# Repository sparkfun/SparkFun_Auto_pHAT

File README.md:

SparkFun Auto pHAT for Raspberry Pi (Qwiic)
========================================

[*SparkFun Auto pHAT for Raspberry Pi (Qwiic) (ROB-16328)*](https://www.sparkfun.com/products/16328)

The SparkFun Auto pHAT for Raspberry Pi is an all in one robotics package that focuses on quickly adding robot functionality and support to your Raspberry Pi or other single-board computer. The Auto pHAT can drive two small DC motors with or without encoders and up to four servo motors in a straightforward manner via an I<sup>2</sup>C connection. The servo control is based on the [SparkFun servo pHAT](https://www.sparkfun.com/products/15316) and thanks to its I<sup>2</sup>C capabilities, this PWM add-on saves the Raspberry Pi's GPIO pins, allowing you to use them for other purposes. We have also provided a Qwiic connector for easy interfacing with the I<sup>2</sup>C bus using the [Qwiic system](https://www.sparkfun.com/qwiic). Whether you use the Auto pHAT with a Raspberry Pi, NVIDIA, Jetson Nano, Google Coral, or other SBC, it makes for a unique robotics addition for and board with a 2x20 GPIO.

The DC motor control comes from the same 4245 PSOC and 2-channel motor ports system used on the [SparkFun Qwiic Motor Driver](https://www.sparkfun.com/products/15451). This provides 1.2A steady state drive per channel (1.5A peak) and 127 levels of DC drive strength. The SparkFun Auto pHAT also supports up to two motor encoders thanks to the onboard ATTINY84A to provide more precise movement to your creation! 

Additionally, the Auto pHAT has an on-board ICM-20948 9DOF IMU for all your motion sensing needs. This enables your robot to access the 3-Axis Gyroscope with four selectable ranges, 3-Axis Accelerometer, again with four selectable ranges, and 3-axis magnetometer with an FSR of ±4900µT.

Power to the SparkFun Auto pHAT can be supplied through USB-C connector or external power. This will power either the motors only, or power the motors as well as the Raspberry Pi that is connected to the HAT. This USB-C connector can also be used to hook up the Pi via serial port connection to avoid having to use a monitor and keyboard for setting up the Pi. We've even added power protection circuits to the design, to avoid damage to power sources.

For reference on programming the ATTINY84:

FUSE BITS:
(Set fuses to run at 8MHz internal)
(Disable Brown Out Detect)

* LowFuse 0xE2 
* HighFuse 0xDF
* ExtendedFuse 0xFF

Repository Contents
-------------------

* **/Documentation** - Data sheets, additional product information
* **/Hardware** - Eagle design files (.brd, .sch)
* **/Hardware/Production** - Production panel files and gerbers (.brd)
* **/Firmware** - Firmware for the Dual Encoder Reader IC (ATTiny84) and the Motor Driver IC (4245 PSOC)

Documentation
--------------

* **[Hookup Guide](https://learn.sparkfun.com/tutorials/sparkfun-auto-phat-hookup-guide)** - Basic hookup guide for the SparkFun Auto pHAT for Raspberry Pi (Qwiic).

License Information
-------------------

This product is _**open source**_! 

Please review the LICENSE.md file for license information. 

If you have any questions or concerns on licensing, please contact technical support on our [SparkFun forums](https://forum.sparkfun.com/viewforum.php?f=152).

Distributed as-is; no warranty is given.

- Your friends at SparkFun.

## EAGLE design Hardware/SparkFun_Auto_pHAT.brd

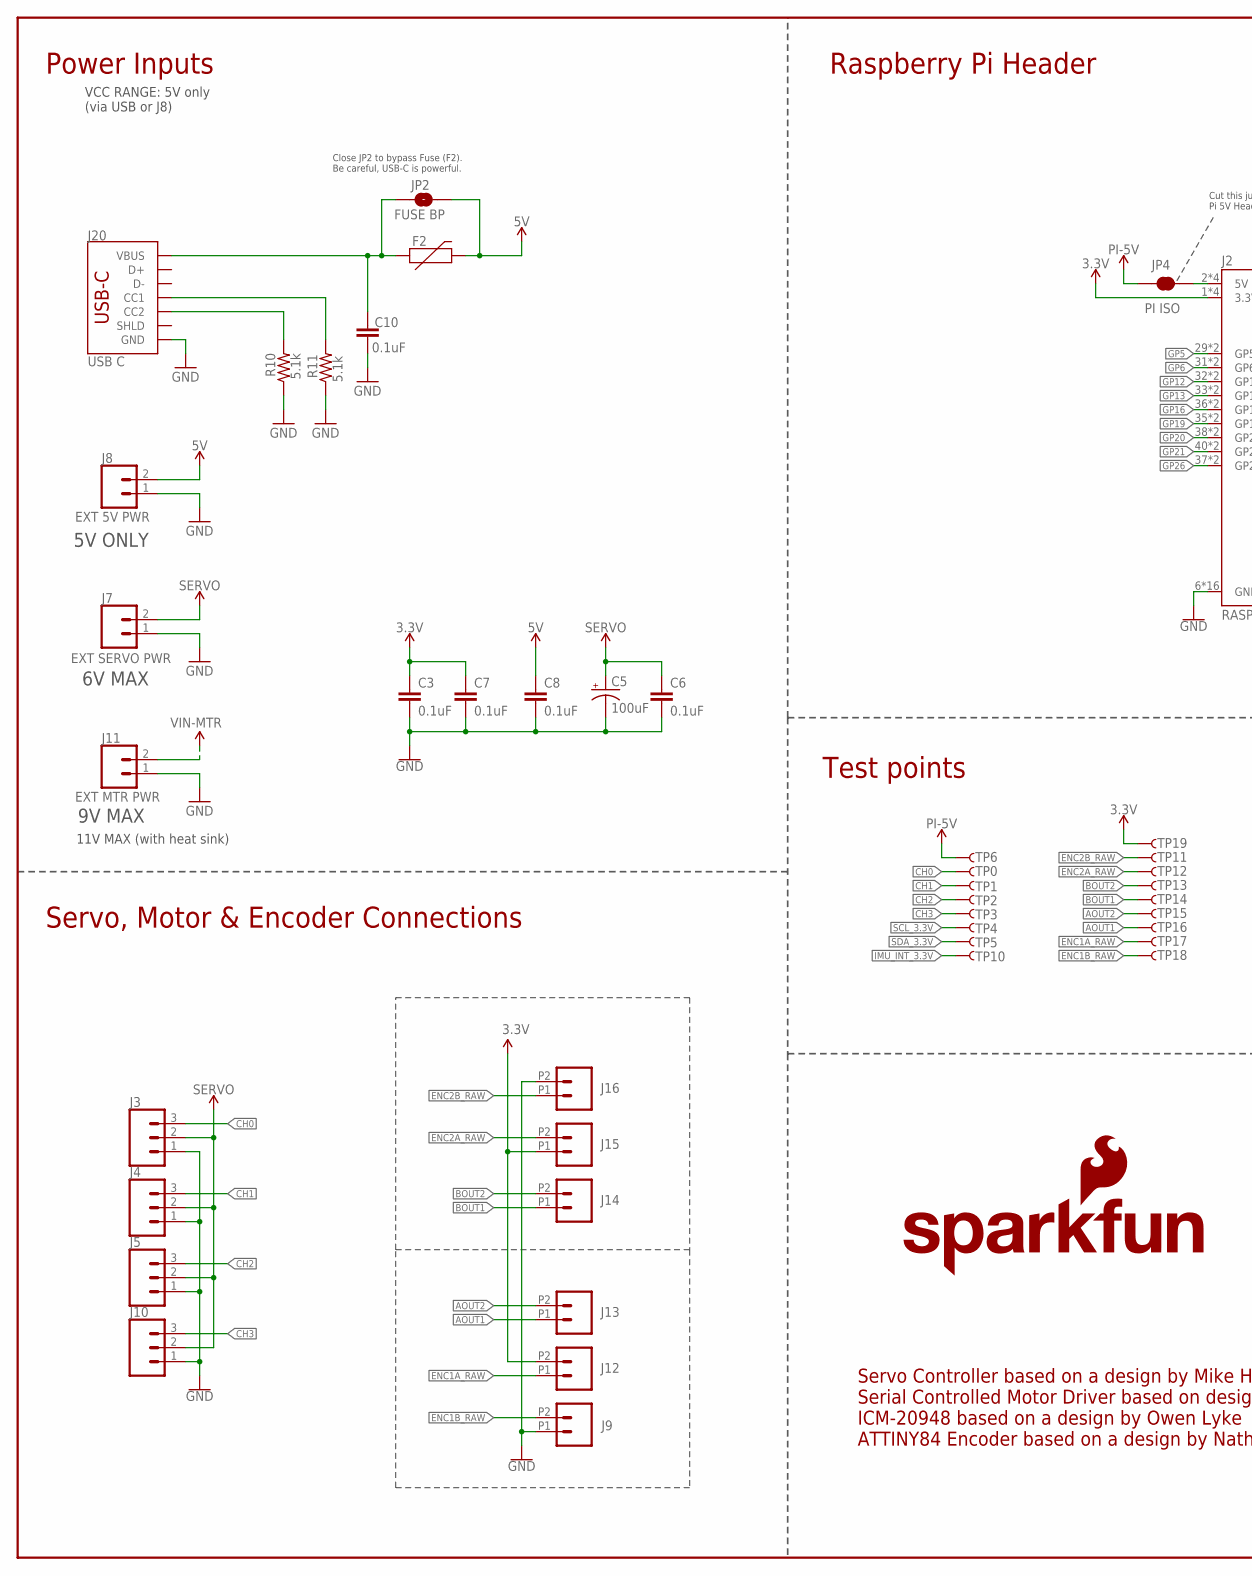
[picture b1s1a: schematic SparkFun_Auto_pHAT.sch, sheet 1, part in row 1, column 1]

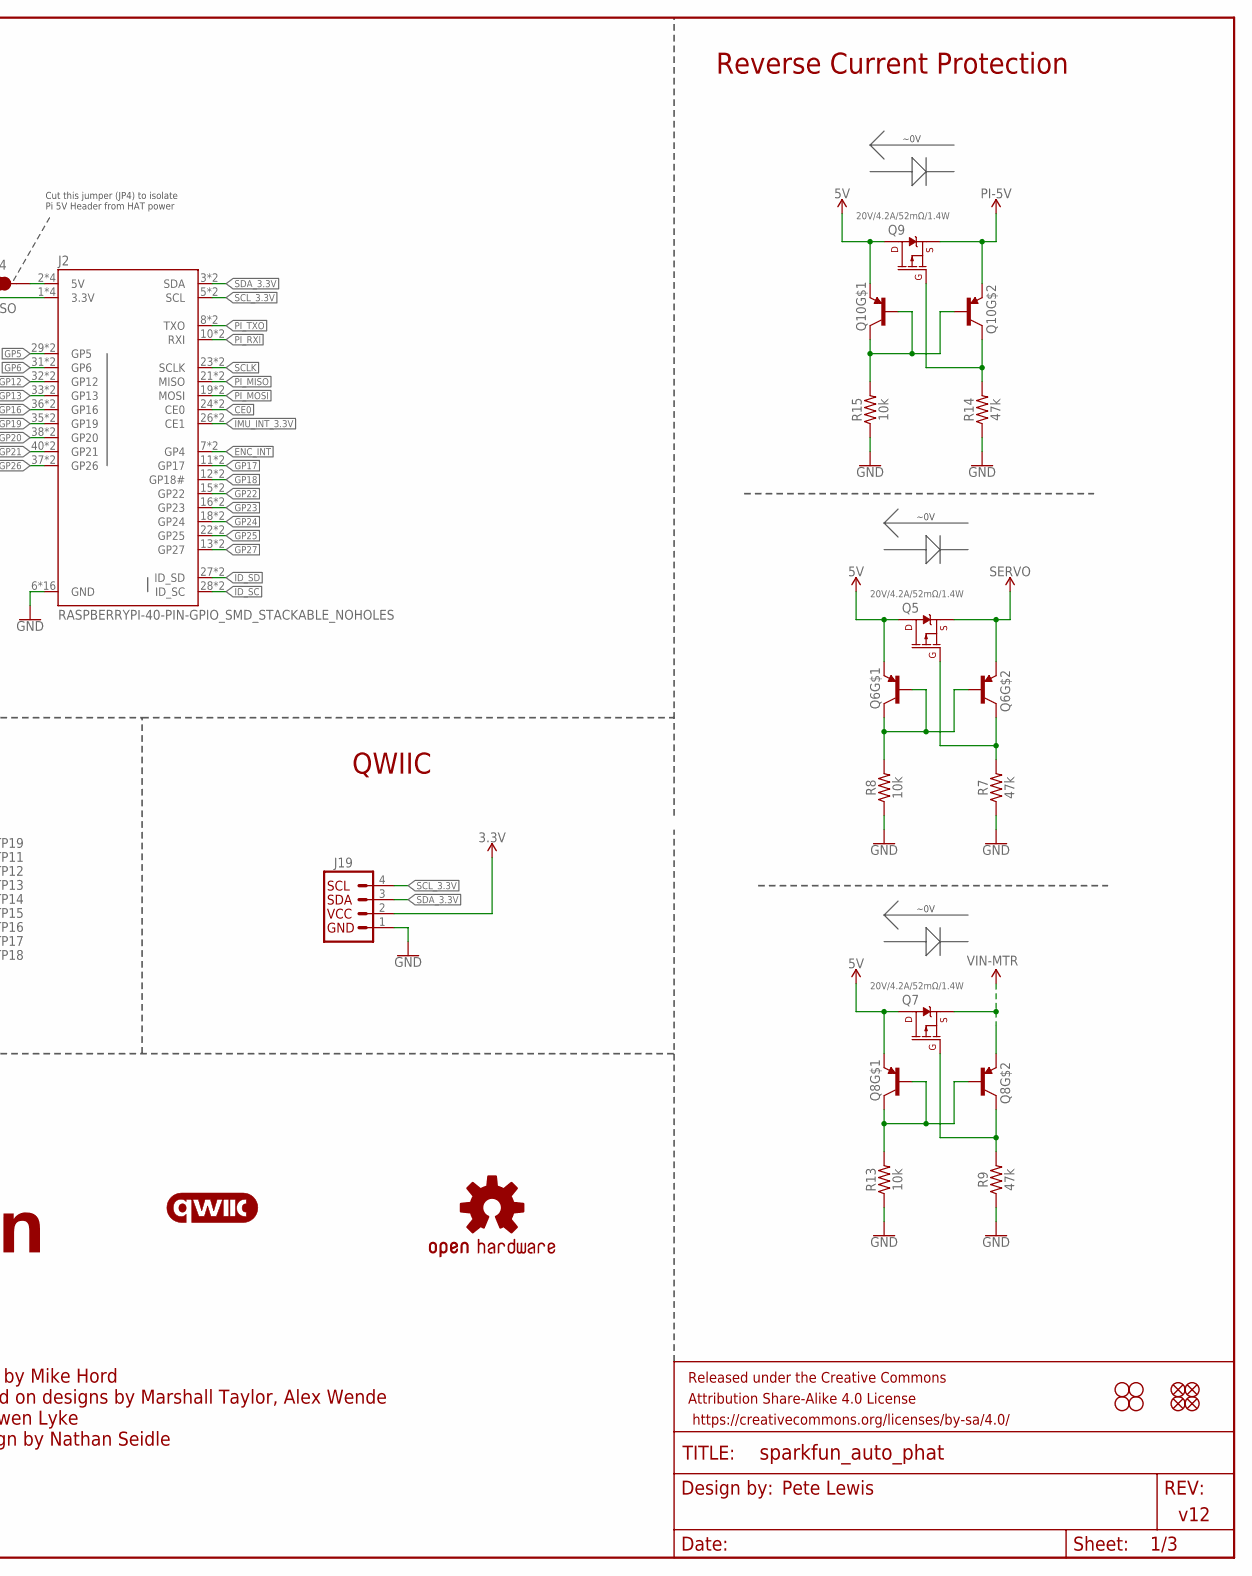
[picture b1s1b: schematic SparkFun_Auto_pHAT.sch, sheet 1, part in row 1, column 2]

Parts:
C3, C6, C7, C8, C10: 0.1uF; 0603
C5: 100uF; PANASONIC_D
F2: 16V/2.5A(5A TRIP); 1812
FD5, FD6, FD7, FD8: FIDUCIALUFIDUCIAL; FIDUCIAL-MICRO
FRAME2: FRAME-LEDGER; CREATIVE_COMMONS
H9, H10, H11, H12: STAND-OFFTIGHT; STAND-OFF-TIGHT
J2: RASPBERRYPI-40-PIN-GPIO_SMD_STACKABLE_NOHOLES; RASPBERRY_PI_HAT_40_PIN_SMD_STACKABLE_NOHOLES
J3, J4, J5, J10: CONN_03LOCK; 1X03_LOCK
J7: EXT SERVO PWR; 1X02
J8: EXT 5V PWR; 1X02
J9, J13, J14, J16: CONN_02LG_DRILL; 1X02_2.54_SCREWTERM_LG_DRILL
J11: EXT MTR PWR; 1X02
J12, J15: CONN_022.54MM_SCREWTERM; 1X02_2.54_SCREWTERM
J19: QWIIC_CONNECTORJS-1MM; JST04_1MM_RA
J20: USB C; USB-C-16P
JP2: FUSE BP; SMT-JUMPER_2_NO_SILK
JP4: PI ISO; SMT-JUMPER_2_NC_TRACE_SILK
LOGO1: SFE_LOGO_NAME_FLAME.1_INCH; SFE_LOGO_NAME_FLAME_.1
LOGO2: OSHW-LOGOS; OSHW-LOGO-S
Q5, Q7, Q9: 20V/4.2A/52mΩ/1.4W; SOT23-3
Q6, Q8, Q10: TRANS_PNP_DUALSOT-363; SOT363_PHILIPS
R7, R9, R14: 47k; 0603@1
R8, R13, R15: 10k; 0603@1
R10, R11: 5.1k; 0603@1
TP0, TP1, TP2, TP3, TP6, TP10, TP11, TP12, TP13, TP14, TP15, TP16, TP17, TP18: TEST-POINT3X4; PAD.03X.04
TP4, TP5, TP19: TEST-POINTTP_15TH_THRU; TP_15TH
U$1: QWIIC_LOGO_5MM; QWIIC_5MM

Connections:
3.3V: C3.1, C7.1, J2.1 (3.3V), J2.1B (3.3V), J2.17 (3.3V), J2.17B (3.3V), J12.P2 (2), J15.P1 (1), J19.2, TP19.P$1; also elsewhere on the board
5V: C8.1, F2.2, J8.2, JP2.2, Q5.3 (D), Q6.1 (E), Q7.3 (D), Q8.1 (E), Q9.3 (D), Q10.1 (E); also elsewhere on the board
!ENC_INT: J2.7 (GP4), J2.7B (GP4); also elsewhere on the board
AOUT1: J13.P1 (1), TP16.P$1; also elsewhere on the board
AOUT2: J13.P2 (2), TP15.P$1; also elsewhere on the board
BOUT1: J14.P1 (1), TP14.P$1; also elsewhere on the board
BOUT2: J14.P2 (2), TP13.P$1; also elsewhere on the board
CC1: J20.A5 (CC1), R11.2
CC2: J20.B5 (CC2), R10.2
CE0: J2.24 (CE0), J2.24B (CE0)
CH0: J3.3, TP0.P$1; also elsewhere on the board
CH1: J4.3, TP1.P$1; also elsewhere on the board
CH2: J5.3, TP2.P$1; also elsewhere on the board
CH3: J10.3, TP3.P$1; also elsewhere on the board
ENC1A_RAW: J12.P1 (1), TP17.P$1; also elsewhere on the board
ENC1B_RAW: J9.P2 (2), TP18.P$1; also elsewhere on the board
ENC2A_RAW: J15.P2 (2), TP12.P$1; also elsewhere on the board
ENC2B_RAW: J16.P1 (1), TP11.P$1; also elsewhere on the board
GND: C3.2, C5.-, C6.2, C7.2, C8.2, C10.2, J2.6 (GND), J2.6B (GND), J2.9 (GND), J2.9B (GND), J2.14 (GND), J2.14B (GND), J2.20 (GND), J2.20B (GND), J2.25 (GND), J2.25B (GND), J2.30 (GND), J2.30B (GND), J2.34 (GND), J2.34B (GND), J2.39 (GND), J2.39B (GND), J3.1, J4.1, J5.1, J7.1, J8.1, J9.P1 (1), J10.1, J11.1, J16.P2 (2), J19.1, J20.GND, J20.GND2 (GND), R7.1, R8.1, R9.1, R10.1, R11.1, R13.1, R14.1, R15.1; also elsewhere on the board
GP5: J2.29 (GP5), J2.29B (GP5)
GP6: J2.31 (GP6), J2.31B (GP6)
GP12: J2.32 (GP12), J2.32B (GP12)
GP13: J2.33 (GP13), J2.33B (GP13)
GP16: J2.36 (GP16), J2.36B (GP16)
GP17: J2.11 (GP17), J2.11B (GP17)
GP18: J2.12 (GP18#), J2.12B (GP18#)
GP19: J2.35 (GP19), J2.35B (GP19)
GP20: J2.38 (GP20), J2.38B (GP20)
GP21: J2.40 (GP21), J2.40B (GP21)
GP22: J2.15 (GP22), J2.15B (GP22)
GP23: J2.16 (GP23), J2.16B (GP23)
GP24: J2.18 (GP24), J2.18B (GP24)
GP25: J2.22 (GP25), J2.22B (GP25)
GP26: J2.37 (GP26), J2.37B (GP26)
GP27: J2.13 (GP27), J2.13B (GP27)
ID_SC: J2.28 (ID_SC), J2.28B (ID_SC)
ID_SD: J2.27 (ID_SD), J2.27B (ID_SD)
IMU_INT_3.3V: J2.26 (CE1), J2.26B (CE1), TP10.P$1; also elsewhere on the board
unnamed: Q5.1 (G), Q6.3 (C), R7.2
unnamed: Q6.2 (B), Q6.5 (B), Q6.6 (C), R8.2
unnamed: Q7.1 (G), Q8.3 (C), R9.2
unnamed: Q8.2 (B), Q8.5 (B), Q8.6 (C), R13.2
unnamed: Q9.1 (G), Q10.3 (C), R14.2
unnamed: Q10.2 (B), Q10.5 (B), Q10.6 (C), R15.2
unnamed: J2.2 (5V), J2.2B (5V), J2.4 (5V), J2.4B (5V), JP4.2
PI-5V: JP4.1, Q9.2 (S), Q10.4 (E), TP6.P$1
PI_MISO: J2.21 (MISO), J2.21B (MISO)
PI_MOSI: J2.19 (MOSI), J2.19B (MOSI)
PI_RXI: J2.10 (RXI), J2.10B (RXI)
PI_TXO: J2.8 (TXO), J2.8B (TXO)
SCLK: J2.23 (SCLK), J2.23B (SCLK)
SCL_3.3V: J2.5 (SCL), J2.5B (SCL), J19.4, TP4.P$1; also elsewhere on the board
SDA_3.3V: J2.3 (SDA), J2.3B (SDA), J19.3, TP5.P$1; also elsewhere on the board
SERVO: C5.+, C6.1, J3.2, J4.2, J5.2, J7.2, J10.2, Q5.2 (S), Q6.4 (E)
VBUS: C10.1, F2.1, J20.VBUS1 (VBUS), J20.VBUS2 (VBUS), JP2.1
VIN-MTR: J11.2, Q7.2 (S), Q8.4 (E); also elsewhere on the board

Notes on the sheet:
Pete Lewis
v12
Raspberry Pi Header
Servo, Motor & Encoder Connections
Cut this jumper (JP4) to isolate Pi 5V Header from HAT power
Power Inputs
Close JP2 to bypass Fuse (F2). Be careful, USB-C is powerful.
VCC RANGE: 5V only (via USB or J8)
~0V
QWIIC
Reverse Current Protection
Test points
9V MAX
6V MAX
5V ONLY
Servo Controller based on a design by Mike Hord Serial Controlled Motor Driver based on designs by Marshall Taylor, Alex Wende ICM-20948 based on a design by Owen Lyke ATTINY84 Encoder based on a design by Nathan Seidle
11V MAX (with heat sink)

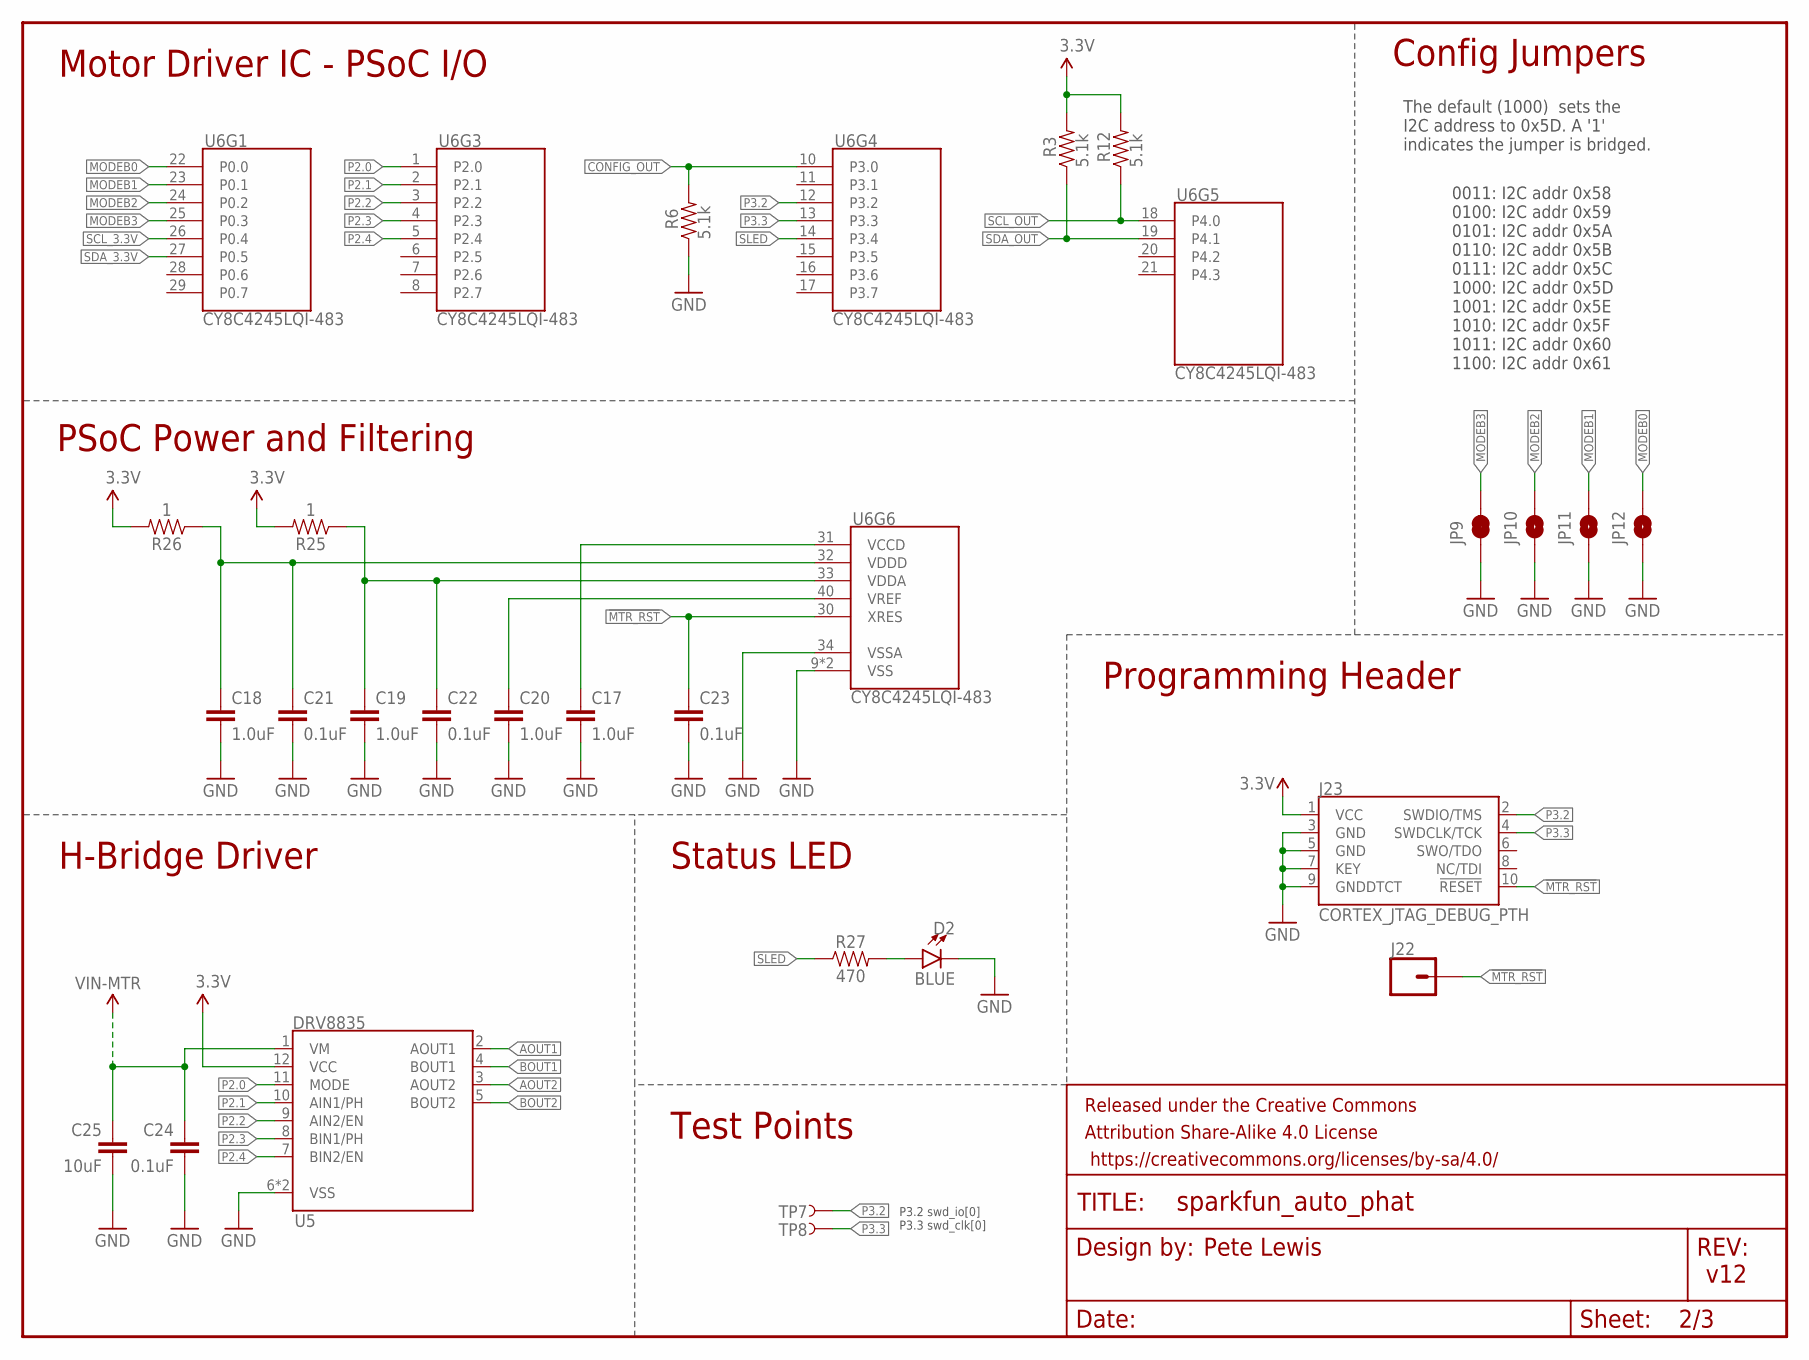
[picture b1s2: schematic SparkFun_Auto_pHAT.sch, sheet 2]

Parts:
C17, C18, C19, C20: 1.0uF; 0402
C21, C22, C23, C24: 0.1uF; 0402
C25: 10uF; 0805
D2: BLUE; LED-0603@1
FRAME1: FRAME-LETTERNO_PACKAGE; DUMMY
J22: CONN_01PTH_NO_SILK_YES_STOP; 1X01_NO_SILK
J23: CORTEX_JTAG_DEBUG_PTH; 2X5-PTH-1.27MM
JP9: JUMPER-PAD-2; SMT-JUMPER_2_NC_TRACE_NO-SILK
JP10, JP11, JP12: JUMPER-PAD-2; SMT-JUMPER_2_NO_NO-SILK
R3, R6, R12: 5.1k; 0603@1
R25, R26: 1; 0603@1
R27: 470; 0603@1
TP7, TP8: TEST-POINT3X4; PAD.03X.04
U5: DRV8835; WSON-12
U6: CY8C4245LQI-483; QFN-40

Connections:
3.3V: J23.1 (VCC), R3.2, R12.2, R25.2, R26.2, U5.12 (VCC); also elsewhere on the board
!MTR_RST: C23.1, J22.1, J23.10 (!RESET), U6.30 (XRES)
AOUT1: U5.2 (AOUT1); also elsewhere on the board
AOUT2: U5.3 (AOUT2); also elsewhere on the board
BOUT1: U5.4 (BOUT1); also elsewhere on the board
BOUT2: U5.5 (BOUT2); also elsewhere on the board
CONFIG_OUT: R6.2, U6.10 (P3.0)
GND: C17.2, C18.2, C19.2, C20.2, C21.2, C22.2, C23.2, C24.2, C25.2, D2.C, J23.3 (GND), J23.5 (GND), J23.7 (KEY), J23.9 (GNDDTCT), JP9.1, JP10.1, JP11.1, JP12.1, R6.1, U5.6 (VSS), U5.PAD (VSS), U6.9 (VSS), U6.34 (VSSA), U6.EP (VSS); also elsewhere on the board
MODEB0: JP12.2, U6.22 (P0.0)
MODEB1: JP11.2, U6.23 (P0.1)
MODEB2: JP10.2, U6.24 (P0.2)
MODEB3: JP9.2, U6.25 (P0.3)
unnamed: C17.1, U6.31 (VCCD)
unnamed: C19.1, C22.1, R25.1, U6.33 (VDDA)
unnamed: C20.1, U6.40 (VREF)
unnamed: D2.A, R27.2
P2.0: U5.11 (MODE), U6.1 (P2.0)
P2.1: U5.10 (AIN1/PH), U6.2 (P2.1)
P2.2: U5.9 (AIN2/EN), U6.3 (P2.2)
P2.3: U5.8 (BIN1/PH), U6.4 (P2.3)
P2.4: U5.7 (BIN2/EN), U6.5 (P2.4)
P3.2: J23.2 (SWDIO/TMS), TP7.P$1, U6.12 (P3.2)
P3.3: J23.4 (SWDCLK/TCK), TP8.P$1, U6.13 (P3.3)
SCL_3.3V: U6.26 (P0.4); also elsewhere on the board
SCL_OUT: R12.1, U6.18 (P4.0)
SDA_3.3V: U6.27 (P0.5); also elsewhere on the board
SDA_OUT: R3.1, U6.19 (P4.1)
SLED: R27.1, U6.14 (P3.4)
VDDD1: C18.1, C21.1, R26.1, U6.32 (VDDD)
VIN-MTR: C24.1, C25.1, U5.1 (VM); also elsewhere on the board

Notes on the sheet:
PSoC Power and Filtering
Config Jumpers
Pete Lewis
Motor Driver IC - PSoC I/O
v12
P3.2 swd_io[0] P3.3 swd_clk[0]
0011: I2C addr 0x58 0100: I2C addr 0x59 0101: I2C addr 0x5A 0110: I2C addr 0x5B 0111: I2C addr 0x5C 1000: I2C addr 0x5D 1001: I2C addr 0x5E 1010: I2C addr 0x5F 1011: I2C addr 0x60 1100: I2C addr 0x61
The default (1000) sets the I2C address to 0x5D. A '1' indicates the jumper is bridged.
Status LED
H-Bridge Driver
Test Points
Programming Header

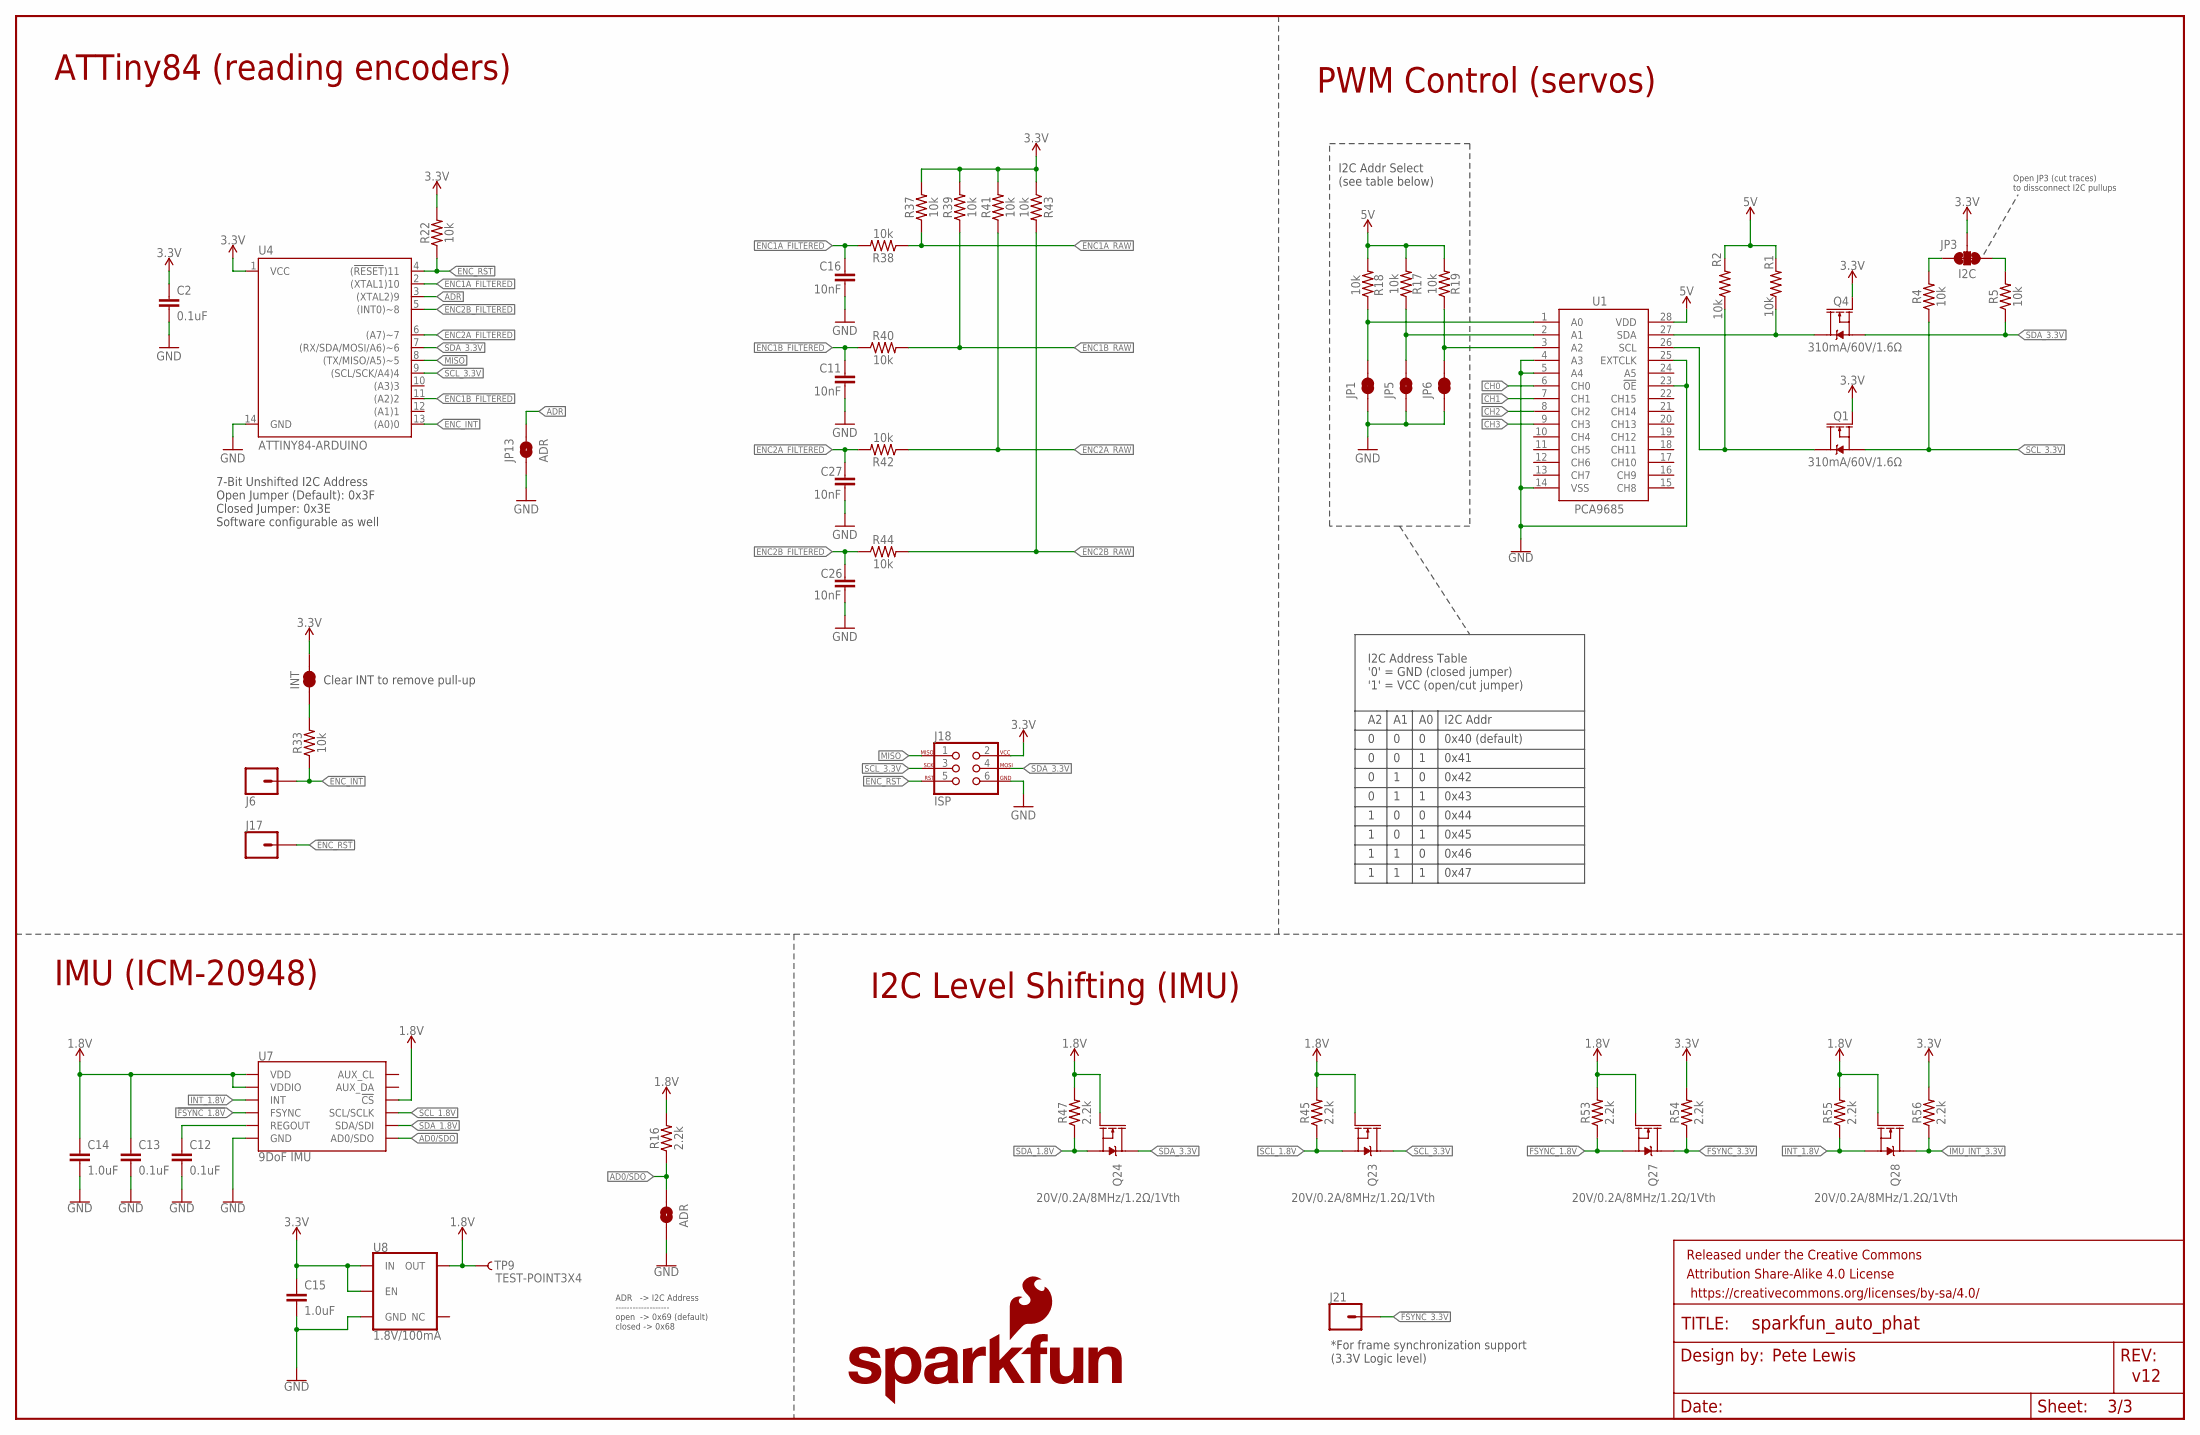
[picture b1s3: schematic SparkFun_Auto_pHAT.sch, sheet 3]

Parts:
C2, C12, C13: 0.1uF; 0603
C11, C16, C26, C27: 10nF; 0603
C14, C15: 1.0uF; 0603
FRAME3: FRAME-LEDGER; CREATIVE_COMMONS
INT: JUMPER-SMT_2_NC_TRACE_SILK; SMT-JUMPER_2_NC_TRACE_SILK
J6, J17, J21: CONN_01PTH_NO_SILK_YES_STOP; 1X01_NO_SILK
J18: ISP; 2X3_TEST_POINTS
JP1, JP5, JP6: JUMPER-PAD-2; SMT-JUMPER_2_NC_TRACE_NO-SILK
JP3: I2C; SMT-JUMPER_3_2-NC_TRACE_SILK
JP13, JP15: ADR; SMT-JUMPER_2_NO_SILK
LOGO4: SFE_LOGO_NAME_FLAME.1_INCH; SFE_LOGO_NAME_FLAME_.1
Q1, Q4: 310mA/60V/1.6Ω; SOT323
Q23, Q24, Q27, Q28: 20V/0.2A/8MHz/1.2Ω/1Vth; SOT-416FL
R1, R2, R4, R5, R17, R18, R19, R22, R33, R37, R38, R39, R40, R41, R42, R43, R44: 10k; 0603@1
R16, R45, R47, R53, R54, R55, R56: 2.2k; 0402-TIGHT
TP9: TEST-POINT3X4; PAD.03X.04
U1: PCA9685; TSSOP-28_4MM
U4: ATTINY84-ARDUINO; SO14
U7: 9DoF IMU; QFN24-3X3
U8: 1.8V/100mA; SC70

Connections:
1.8V: C13.1, C14.1, Q23.1 (G), Q24.1 (G), Q27.1 (G), Q28.1 (G), R16.2, R45.2, R47.2, R53.2, R55.2, TP9.P$1, U7.8 (VDDIO), U7.13 (VDD), U7.22 (!CS), U8.5 (OUT)
3.3V: C2.1, C15.1, INT.2, J18.2, JP3.2, Q1.1 (G), Q4.1 (G), R22.2, R37.2, R39.2, R41.2, R43.1, R54.2, R56.2, U4.1 (VCC), U8.1 (IN), U8.3 (EN); also elsewhere on the board
5V: R1.2, R2.2, R17.2, R18.2, R19.2, U1.28 (VDD); also elsewhere on the board
!ENC_INT: J6.1, R33.1, U4.13 ((A0)0); also elsewhere on the board
!ENC_RST: J17.1, J18.5, R22.1, U4.4 ((!RESET!)11)
!FSYNC_1.8V: Q27.2 (S), R53.1, U7.11 (FSYNC)
!FSYNC_3.3V: J21.1, Q27.3 (D), R54.1
AD0/SDO: JP15.2, R16.1, U7.9 (AD0/SDO)
ADD_A0: JP1.2, R18.1, U1.1 (A0)
ADD_A1: JP5.2, R17.1, U1.2 (A1)
ADD_A2: JP6.2, R19.1, U1.3 (A2)
ADR: JP13.2, U4.3 ((XTAL2)9)
CH0: U1.6 (CH0); also elsewhere on the board
CH1: U1.7 (CH1); also elsewhere on the board
CH2: U1.8 (CH2); also elsewhere on the board
CH3: U1.9 (CH3); also elsewhere on the board
ENC1A_FILTERED: C16.1, R38.2, U4.2 ((XTAL1)10)
ENC1A_RAW: R37.1, R38.1; also elsewhere on the board
ENC1B_FILTERED: C11.1, R40.1, U4.11 ((A2)2)
ENC1B_RAW: R39.1, R40.2; also elsewhere on the board
ENC2A_FILTERED: C27.1, R42.2, U4.6 ((A7)~7)
ENC2A_RAW: R41.1, R42.1; also elsewhere on the board
ENC2B_FILTERED: C26.1, R44.1, U4.5 ((INT0)~8)
ENC2B_RAW: R43.2, R44.2; also elsewhere on the board
GND: C2.2, C11.2, C12.2, C13.2, C14.2, C15.2, C16.2, C26.2, C27.2, J18.6, JP1.1, JP5.1, JP6.1, JP13.1, JP15.1, U1.4 (A3), U1.5 (A4), U1.14 (VSS), U1.23 (!OE), U1.25 (EXTCLK), U4.14 (GND), U7.18 (GND), U7.20 (GND), U8.2 (GND); also elsewhere on the board
IMU_INT_3.3V: Q28.3 (D), R56.1; also elsewhere on the board
INT_1.8V: Q28.2 (S), R55.1, U7.12 (INT)
INT_R: INT.1, R33.2
MISO: J18.1, U4.8 ((TX/MISO/A5)~5)
unnamed: JP3.3, R4.2
unnamed: Q1.3 (D), R2.1, U1.26 (SCL)
unnamed: Q4.3 (D), R1.1, U1.27 (SDA)
unnamed: JP3.1, R5.2
unnamed: C12.1, U7.10 (REGOUT)
SCL_1.8V: Q23.2 (S), R45.1, U7.23 (SCL/SCLK)
SCL_3.3V: J18.3, Q1.2 (S), Q23.3 (D), R4.1, U4.9 ((SCL/SCK/A4)4); also elsewhere on the board
SDA_1.8V: Q24.2 (S), R47.1, U7.24 (SDA/SDI)
SDA_3.3V: J18.4, Q4.2 (S), Q24.3 (D), R5.1, U4.7 ((RX/SDA/MOSI/A6)~6); also elsewhere on the board

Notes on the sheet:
IMU (ICM-20948)
I2C Level Shifting (IMU)
ADR -> I2C Address ------------------- open -> 0x69 (default) closed -> 0x68
7-Bit Unshifted I2C Address Open Jumper (Default): 0x3F Closed Jumper: 0x3E Software configurable as well
Clear INT to remove pull-up
ATTiny84 (reading encoders)
I2C Addr
Open JP3 (cut traces) to dissconnect I2C pullups
PWM Control (servos)
*For frame synchronization support (3.3V Logic level)
v12
Pete Lewis
I2C Addr Select (see table below)
0x40 (default)
0x41
0x42
0x43
0x44
0x45
0x46
0x47
I2C Address Table '0' = GND (closed jumper) '1' = VCC (open/cut jumper)

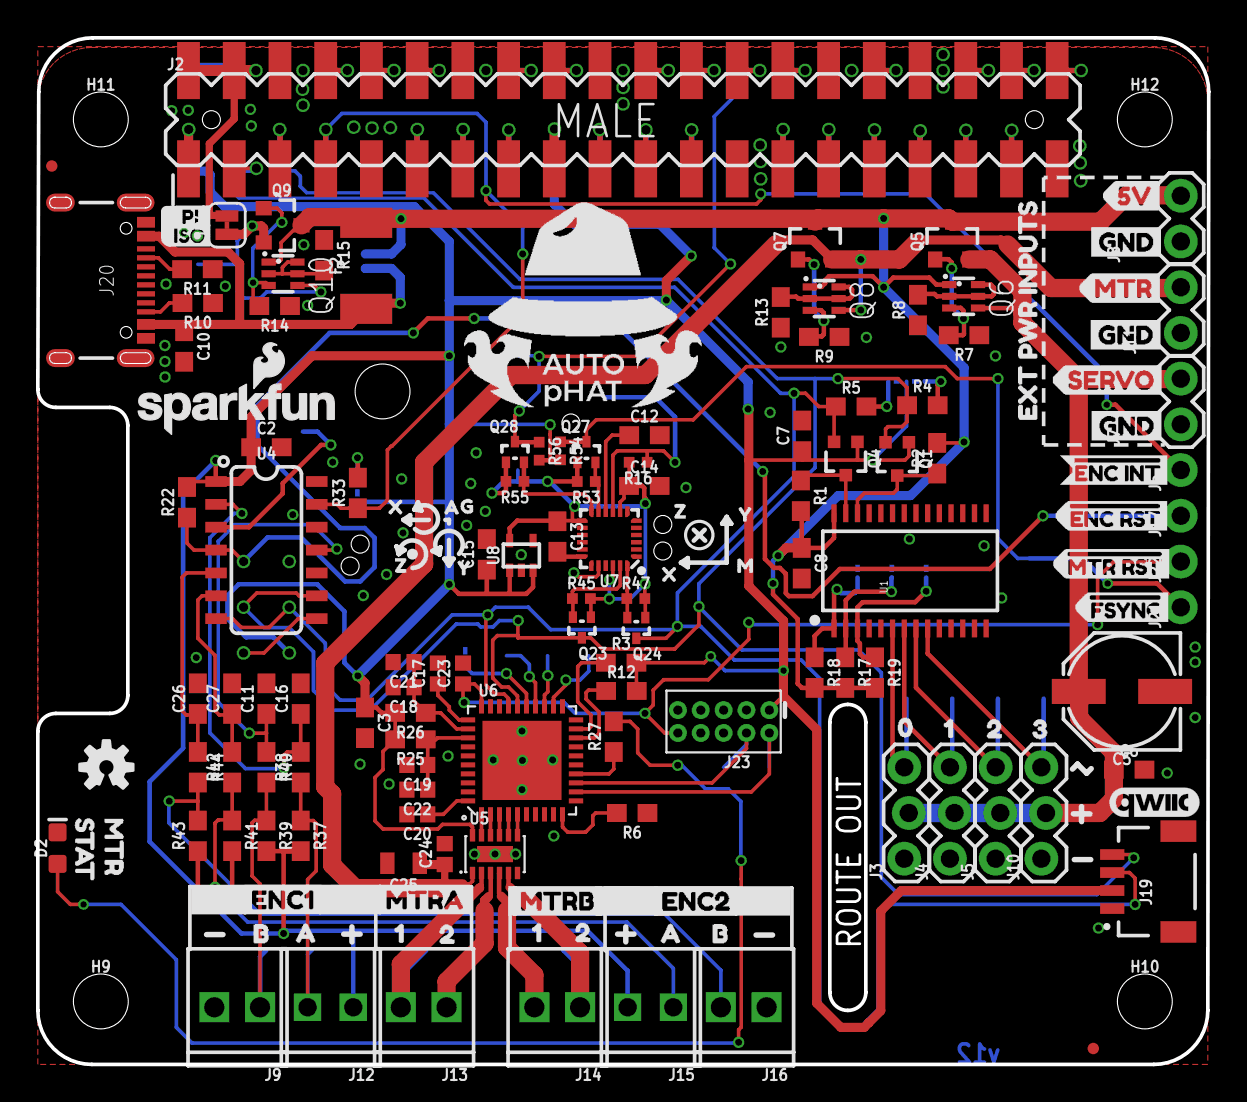
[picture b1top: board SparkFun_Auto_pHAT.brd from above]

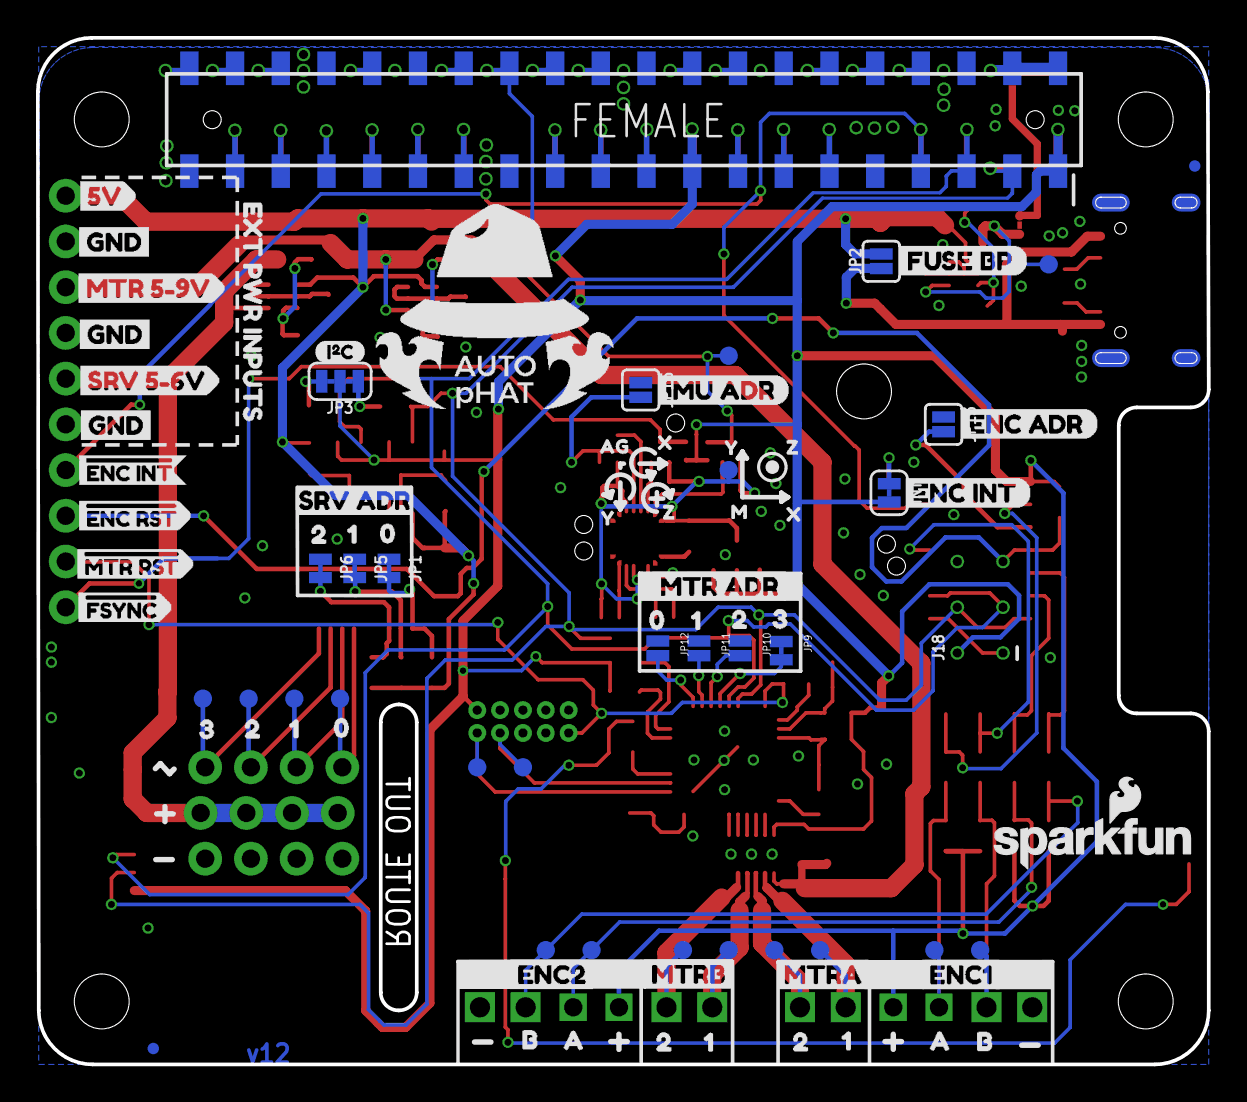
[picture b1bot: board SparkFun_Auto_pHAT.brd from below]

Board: 2 copper layers, 65.1 x 57.0 mm, 246 parts (84 on the bottom side), 100 nets.

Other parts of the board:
U$2: I_SUPER2_C-()-03
U$3, U$4, U$5, U$59, U$60, U$61: GND3
U$6, U$7, U$75, U$76: 10
U$8, U$79: 00
U$9: #MTR_RST5
U$10: #FSYNC7
U$11: #ENC_RST4
U$12: #ENC_INT6
U$13, U$52: EXT_PWR_INPUTS3
U$14: 5V2
U$15: MTR1
U$16: SERVO0
U$17, U$82: 11
U$18, U$19: 1X06_2.54_SCREWTERM_PIN_REF
U$20, U$21, U$65, U$66: B15
U$22, U$67: ENC112
U$23, U$68: ENC213
U$24, U$80: 22
U$25, U$81: 33
U$26, U$27, U$69, U$70: A14
U$29: STAT4
U$30: SRV_5#6V1
U$31, U$73: MTRA0
U$32: ISO1
U$33, U$41: 05
U$34, U$42: 16
U$35: PI0
U$36, U$45: 27
U$37: 38
U$38: MTR_5#9V0
U$39: IMU_ADR9
U$40, U$74: MTRB1
U$43, U$44, U$77, U$78: 21
U$46: MTR0
U$47: SRV_ADR0
U$48: ENC_INT12
U$49: ENC_ADR11
U$50: FUSE_BP10
U$51: MTR_ADR0
U$53: 5V3
U$56: #ENC_RST6
U$57: #MTR_RST7
U$58: #FSYNC8
U$62: #ENC_INT0
U$83, U$85: AUTOHAT-LOGO
U$103, U$109, U$123, U$126: X0
U$104, U$110, U$124, U$127: Y1
U$105, U$111, U$125, U$128: Z2
U$106, U$129: G5
U$107, U$130: A4
U$108, U$122: M3

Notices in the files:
parts and their libraries:
SparkFun-Capacitors: Licensing: Creative Commons ShareAlike 4.0 International - https://creativecommons.org/licenses/by-sa/4.0
SparkFun-Aesthetics: Released under the Creative Commons Attribution Share-Alike 4.0 License
SparkFun-Aesthetics: https://creativecommons.org/licenses/by-sa/4.0
